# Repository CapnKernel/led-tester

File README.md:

# led-tester
A circuit to characterise the behaviour of LEDs.

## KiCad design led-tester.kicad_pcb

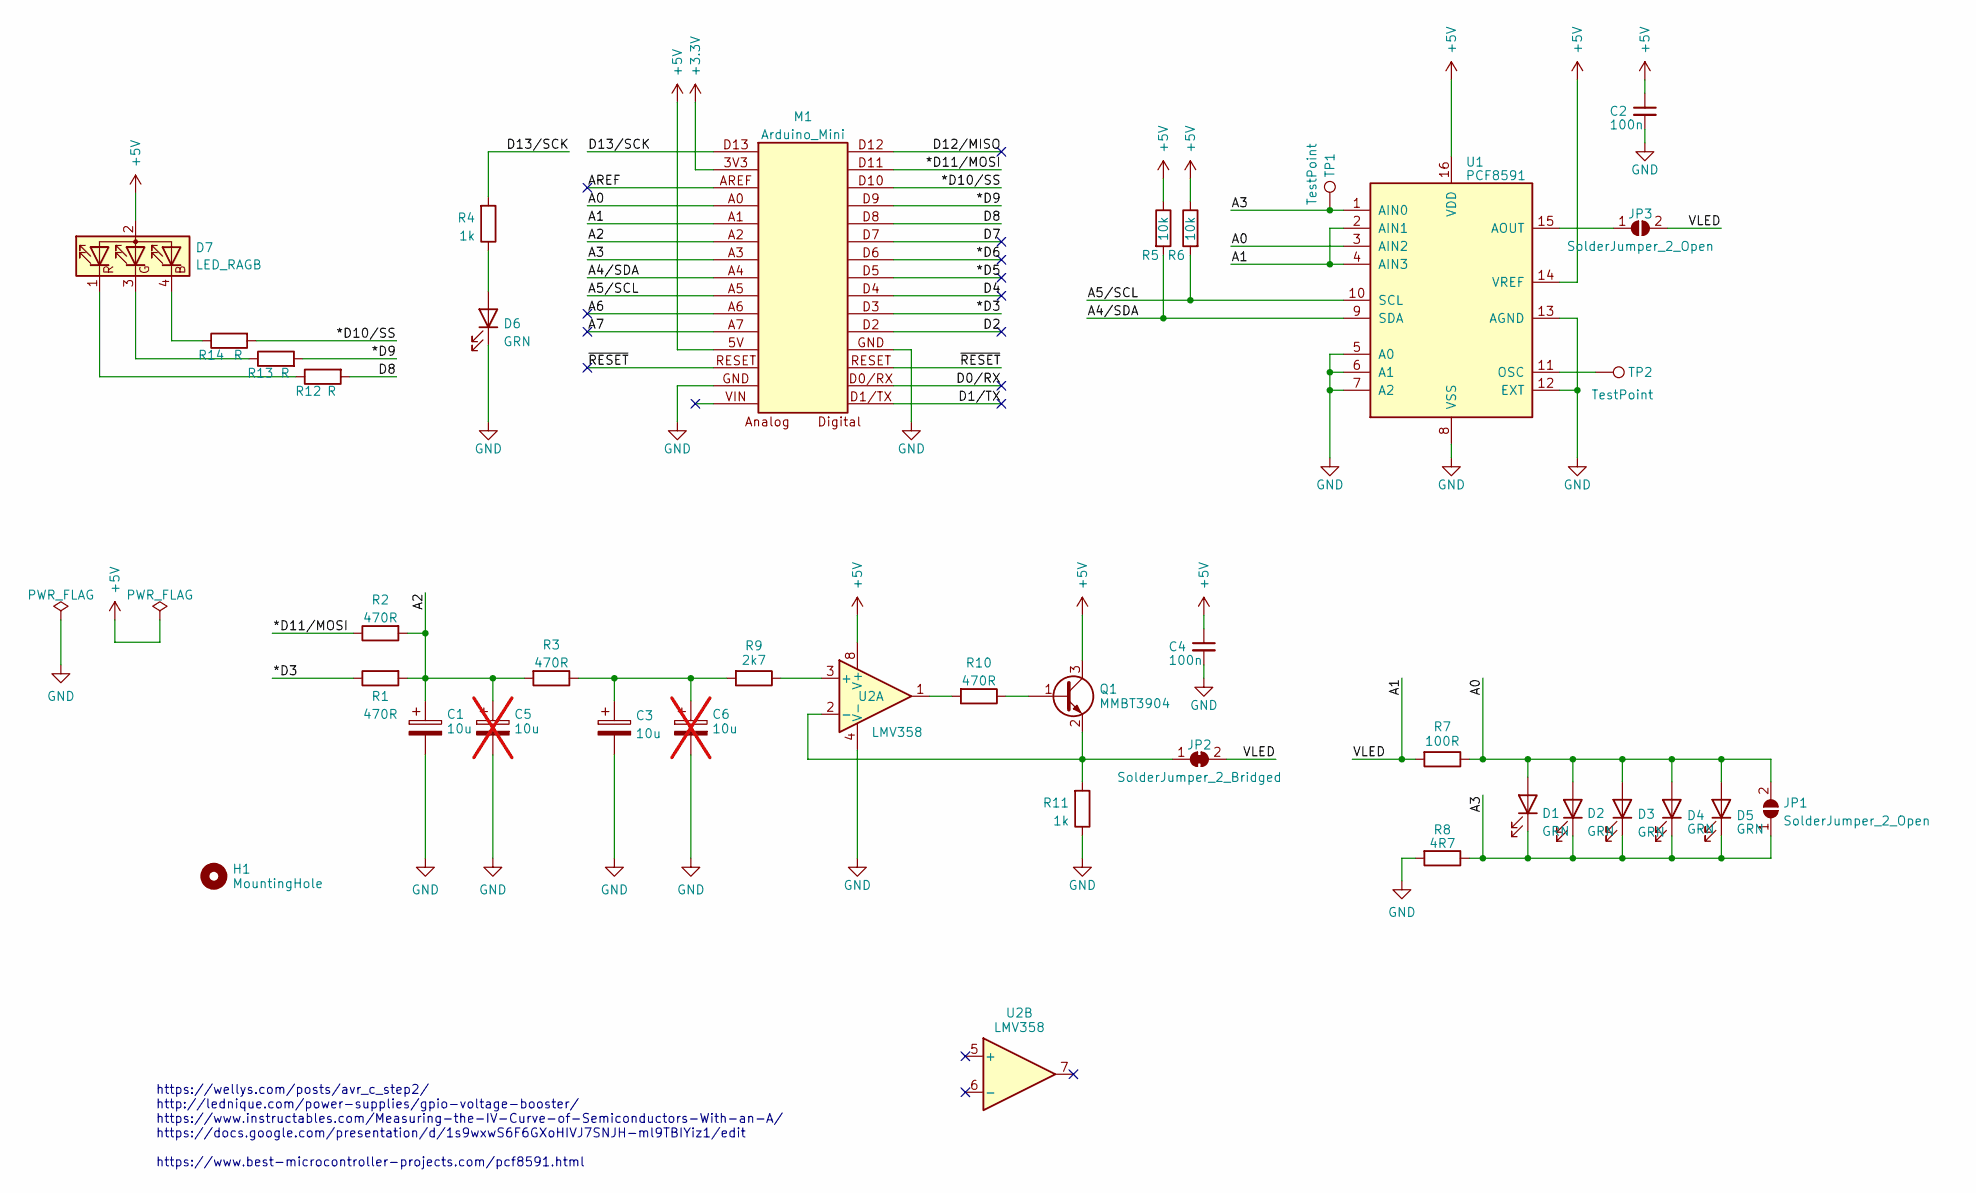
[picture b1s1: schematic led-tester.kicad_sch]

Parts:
C1, C3: 10u; CP_Radial_D5.0mm_P2.00mm
C2, C4: 100n; C_0805_2012Metric_Pad1.18x1.45mm_HandSolder
C5, C6: 10u; C_0805_2012Metric_Pad1.18x1.45mm_HandSolder; not fitted
D1: GRN; LED_0603_1608Metric_Pad1.05x0.95mm_HandSolder
D2, D6: GRN; LED_0805_2012Metric_Pad1.15x1.40mm_HandSolder
D3: GRN; LED_1206_3216Metric_Pad1.42x1.75mm_HandSolder
D4: GRN; PinHeader_1x02_P2.54mm_Vertical
D5: GRN; LED_D5.0mm
D7: LED_RAGB; LED_D8.0mm-4_RGB
H1: MountingHole; AlignmentSlot
JP1: SolderJumper_2_Open; TestPad
JP2: SolderJumper_2_Bridged; SolderJumper-2_P1.3mm_Bridged_Pad1.0x1.5mm
JP3: SolderJumper_2_Open; SolderJumper-2_P1.3mm_Open_Pad1.0x1.5mm
M1: Arduino_Mini; Arduino Mini
Q1: MMBT3904; SOT-23
R1, R2, R3, R10: 470R; R_0805_2012Metric_Pad1.20x1.40mm_HandSolder
R4, R11: 1k; R_0805_2012Metric_Pad1.20x1.40mm_HandSolder
R5, R6: 10k; R_0805_2012Metric_Pad1.20x1.40mm_HandSolder
R7: 100R; R_0805_2012Metric_Pad1.20x1.40mm_HandSolder
R8: 4R7; R_0805_2012Metric_Pad1.20x1.40mm_HandSolder
R9: 2k7; R_0805_2012Metric_Pad1.20x1.40mm_HandSolder
R12, R13, R14: R; R_0603_1608Metric
TP1: TestPoint; TestPoint_THTPad_D2.0mm_Drill1.0mm
TP2: TestPoint; TestPoint_Pad_1.5x1.5mm
U1: PCF8591; SOIC-16W_7.5x10.3mm_P1.27mm
U2: LMV358; SOIC-8_3.9x4.9mm_P1.27mm

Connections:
+3.3V: M1.3V3
+5V: C2.1, C4.1, D7.2 (A), M1.5V, Q1.3 (C), R5.1, R6.1, U1.14 (VREF), U1.16 (VDD), U2.8 (V+)
/*D3: M1.D3, R1.1
/*D5: M1.D5
/*D6: M1.D6
/*D9: M1.D9, R13.2
/*D10/SS: M1.D10, R14.2
/*D11/MOSI: M1.D11, R2.1
/A0: D1.2 (A), D2.2 (A), D3.2 (A), D4.2 (A), D5.2 (A), JP1.2 (B), M1.A0, R7.1, U1.3 (AIN2)
/A1: JP2.2 (B), JP3.2 (B), M1.A1, R7.2, U1.2 (AIN1), U1.4 (AIN3)
/A2: C1.1, C5.1, M1.A2, R1.2, R2.2, R3.2
/A3: D1.1 (K), D2.1 (K), D3.1 (K), D4.1 (K), D5.1 (K), JP1.1 (A), M1.A3, R8.1, TP1.1, U1.1 (AIN0)
/A4/SDA: M1.A4, R5.2, U1.9 (SDA)
/A5/SCL: M1.A5, R6.2, U1.10 (SCL)
/A6: M1.A6
/A7: M1.A7
/AREF: M1.AREF
/D0/RX: M1.D0/RX
/D1/TX: M1.D1/TX
/D2: M1.D2
/D4: M1.D4
/D7: M1.D7
/D8: M1.D8, R12.2
/D12/MISO: M1.D12
/D13/SCK: M1.D13, R4.2
/~RESET: M1.RESET
GND: C1.2, C2.2, C3.2, C4.2, C5.2, C6.2, D6.1 (K), M1.GND, R8.2, R11.1, U1.5 (A0), U1.6 (A1), U1.7 (A2), U1.8 (VSS), U1.12 (EXT), U1.13 (AGND), U2.4 (V-)
unnamed: C3.1, C6.1, R3.1, R9.2
unnamed: D6.2 (A), R4.1
unnamed: D7.4 (BK), R14.1
unnamed: D7.3 (GK), R13.1
unnamed: D7.1 (RK), R12.1
unnamed: JP2.1 (A), Q1.2 (E), R11.2, U2.2 (-)
unnamed: JP3.1 (A), U1.15 (AOUT)
unnamed: Q1.1 (B), R10.1
unnamed: R10.2, U2.1
unnamed: TP2.1, U1.11 (OSC)
unnamed: R9.1, U2.3 (+)

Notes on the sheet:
https://wellys.com/posts/avr_c_step2/ http://lednique.com/power-supplies/gpio-voltage-booster/ https://www.instructables.com/Measuring-the-IV-Curve-of-Semiconductors-With-an-A/ https://docs.google.com/presentation/d/1s9wxwS6F6GXoHIVJ7SNJH-ml9TBIYiz1/edit https://www.best-microcontroller-projects.co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

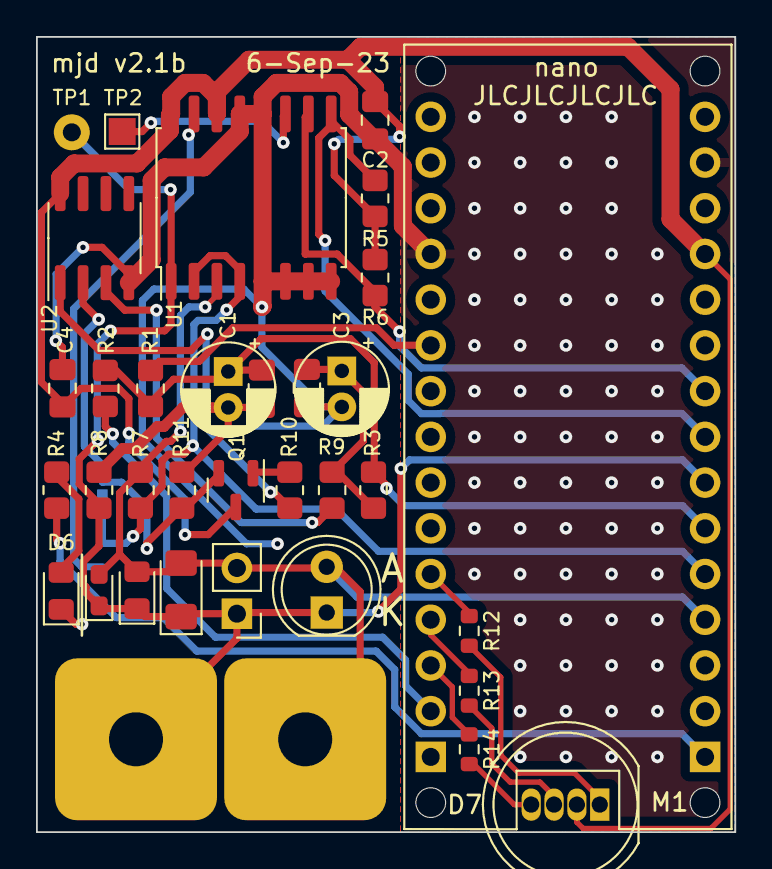
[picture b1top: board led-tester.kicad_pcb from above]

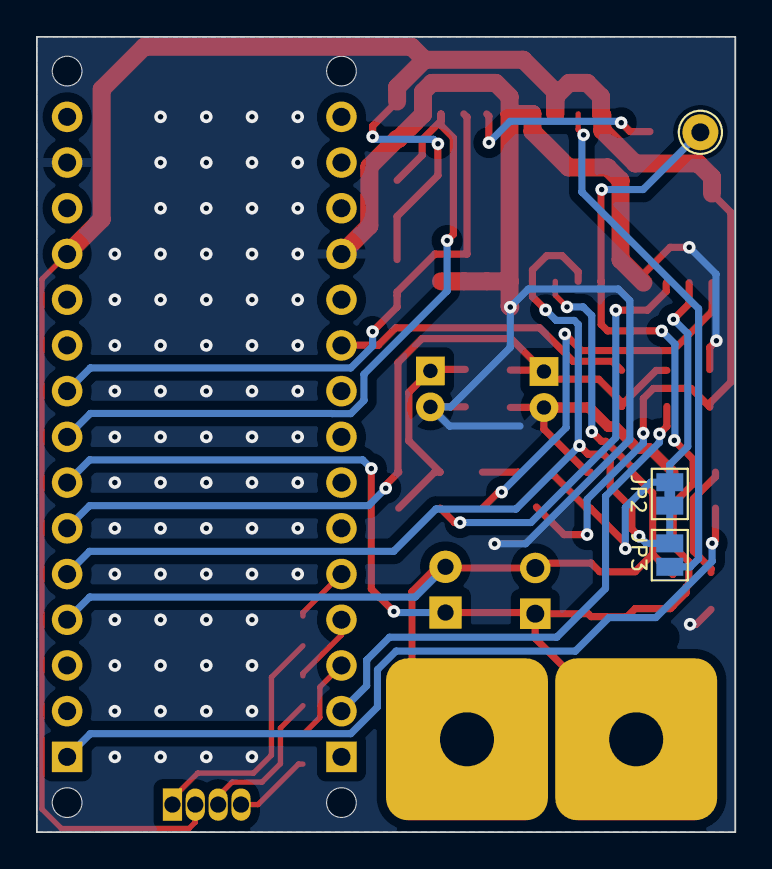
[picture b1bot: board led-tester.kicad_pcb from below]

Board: 2 copper layers, 38.8 x 44.2 mm, 37 parts (3 on the bottom side), 25 nets.

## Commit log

2023-05-02 Added a current sense resistor, a decoupling cap, and rewired the PCF8591 analog inputs.
2023-05-04 Added a sense resistor between the LED under test, and GND.
2023-05-10 Added .gitignore, changed output directory.
2023-07-04 Complete redesign to add op-amp buffer, 2-stage LP filter and fit in 5x5cm.
2023-08-29 Added a common-anode RGB LED.
2023-09-06 Marked unused op-amp pins as NC.
2023-09-06 Hide RGB LED and resistors from 3d view, and move designators
2023-09-06 News caps plus tweaks
    Added SMD caps as alternatives to THT
    Updated footprints from library
    Separator on silk between power LED and test LEDs.
2023-09-06 Oops, files that went to JLC did not have designators in silkscreen.
